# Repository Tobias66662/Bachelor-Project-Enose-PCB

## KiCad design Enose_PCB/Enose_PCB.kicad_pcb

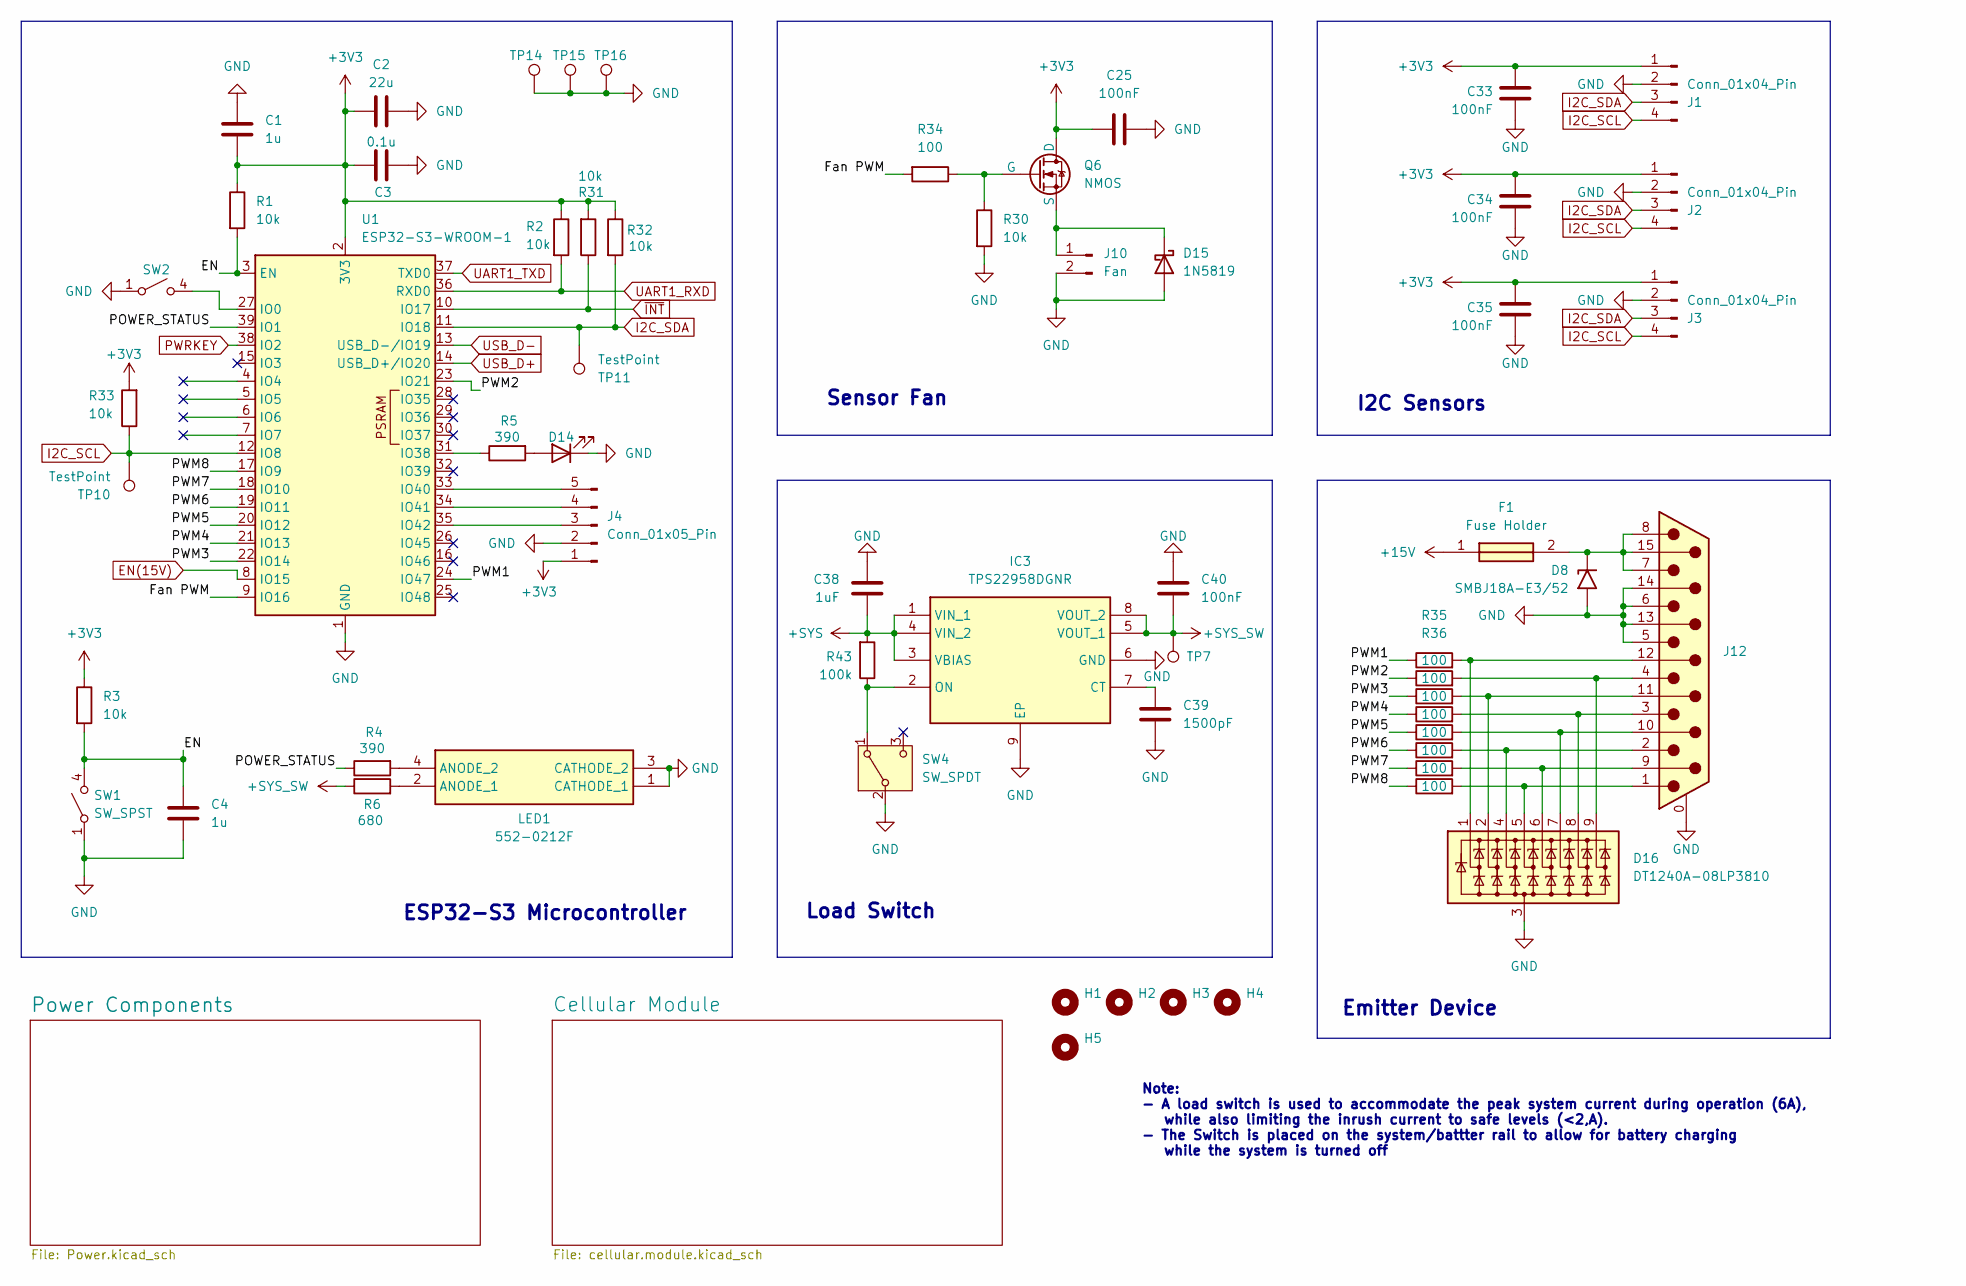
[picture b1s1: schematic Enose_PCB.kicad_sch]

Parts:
C1, C4: 1u; C_0805_2012Metric_Pad1.18x1.45mm_HandSolder
C2: 22u; C_0805_2012Metric_Pad1.18x1.45mm_HandSolder
C3: 0.1u; C_0805_2012Metric_Pad1.18x1.45mm_HandSolder
C25, C33, C34, C35, C40: 100nF; C_0805_2012Metric_Pad1.18x1.45mm_HandSolder
C38: 1uF; C_0805_2012Metric_Pad1.18x1.45mm_HandSolder
C39: 1500pF; C_0805_2012Metric_Pad1.18x1.45mm_HandSolder
D8: SMBJ18A-E3/52; D_SMB
D14: LED Amber; LED_0805_2012Metric_Pad1.15x1.40mm_HandSolder
D15: 1N5819; D_SOD-123
D16: DT1240A-08LP3810; UDFN-9_1.0x3.8mm_P0.5mm
F1: Fuse Holder; 64600001223; Mouser Part Number 576-64600001223
H1, H2, H3, H4, H5: MountingHole; MountingHole_3.2mm_M3
IC3: TPS22958DGNR; SOP65P490X110-9N; Mouser Part Number 595-TPS22958DGNR
J1: Conn_01x04_Pin; PinHeader_1x04_P2.54mm_Vertical
J2, J3: Conn_01x04_Pin; JST_XH_B4B-XH-A_1x04_P2.50mm_Vertical
J4: Conn_01x05_Pin; PinHeader_1x05_P2.54mm_Vertical
J10: Fan; JST_XH_B2B-XH-AM_1x02_P2.50mm_Vertical
J12: DA15_Pins_MountingHoles; 6E17C015PAJ121
LED1: 552-0212F; 5520212F; Mouser Part Number 645-552-0212F
Q6: NMOS; SOT-23-3
R1, R2, R3, R30, R31, R32, R33: 10k; R_0805_2012Metric_Pad1.20x1.40mm_HandSolder
R4, R5: 390; R_0805_2012Metric_Pad1.20x1.40mm_HandSolder
R6: 680; R_0805_2012Metric_Pad1.20x1.40mm_HandSolder
R34, R35, R36, R37, R38, R39, R40, R41, R42: 100; R_0805_2012Metric_Pad1.20x1.40mm_HandSolder
R43: 100k; R_0805_2012Metric_Pad1.20x1.40mm_HandSolder
SW1, SW2: SW_SPST; 430181038816
SW4: SW_SPDT; OS102011MA1QN1
TP7, TP10, TP11, TP14, TP15, TP16: TestPoint; TestPoint_Pad_D1.5mm
U1: ESP32-S3-WROOM-1

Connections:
+3V3: C1.1, C2.1, C3.2, C25.2, C33.1, C34.1, C35.1, J1.1, J2.1, J3.1, J4.1, Q6.1 (D), R1.1, R2.1, R3.1, R31.2, R32.1, R33.2, U1.2 (3V3); also elsewhere on the board
+15V: F1.1; also elsewhere on the board
+SYS: C38.2, IC3.1 (VIN_1), IC3.3 (VBIAS), IC3.4 (VIN_2), R43.2; also elsewhere on the board
+SYS_SW: C40.2, IC3.5 (VOUT_1), IC3.8 (VOUT_2), R6.1, TP7.1; also elsewhere on the board
/EN: C4.1, R1.2, R3.2, SW1.4 (B), U1.3 (EN)
/Fan PWM: R34.2, U1.9 (IO16)
/POWER_STATUS: R4.1, U1.39 (IO1)
/PWM1: R35.1, U1.24 (IO47)
/PWM2: R36.1, U1.23 (IO21)
/PWM3: R37.1, U1.22 (IO14)
/PWM4: R38.1, U1.21 (IO13)
/PWM5: R39.1, U1.20 (IO12)
/PWM6: R40.1, U1.19 (IO11)
/PWM7: R41.1, U1.18 (IO10)
/PWM8: R42.1, U1.17 (IO9)
EN(15V): U1.8 (IO15); also elsewhere on the board
GND: C1.2, C2.2, C3.1, C4.2, C25.1, C33.2, C34.2, C35.2, C38.1, C39.2, C40.1, D8.2 (A2), D14.1 (K), D15.2 (A), D16.3 (A), IC3.6 (GND), IC3.9 (EP), J1.2, J2.2, J3.2, J4.2, J10.2, J12.0 (PAD), J12.5, J12.6, J12.13, J12.14, LED1.1 (CATHODE_1), LED1.3 (CATHODE_2), R30.2, SW1.1 (A), SW2.1 (A), SW4.2 (B), TP14.1, TP15.1, TP16.1, U1.1 (GND), U1.40 (GND), U1.41 (GND); also elsewhere on the board
I2C_SCL: J1.4, J2.4, J3.4, R33.1, TP10.1, U1.12 (IO8); also elsewhere on the board
I2C_SDA: J1.3, J2.3, J3.3, R32.2, TP11.1, U1.11 (IO18); also elsewhere on the board
unnamed: D8.1 (A1), F1.2, J12.7, J12.8, J12.15
unnamed: D14.2 (A), R5.2
unnamed: D15.1 (K), J10.1, Q6.3 (S)
unnamed: D16.1 (K1), J12.12, R35.2
unnamed: D16.2 (K2), J12.11 (P111), R37.2
unnamed: D16.4 (K3), J12.2, R40.2
unnamed: D16.5 (K4), J12.1, R42.2
unnamed: D16.6 (K5), J12.9, R41.2
unnamed: D16.7 (K6), J12.10, R39.2
unnamed: D16.8 (K7), J12.3, R38.2
unnamed: D16.9 (K8), J12.4, R36.2
unnamed: C39.1, IC3.7 (CT)
unnamed: IC3.2 (ON), R43.1, SW4.1 (A)
unnamed: J4.3, U1.35 (IO42)
unnamed: J4.4, U1.34 (IO41)
unnamed: J4.5, U1.33 (IO40)
unnamed: LED1.2 (ANODE_1), R6.2
unnamed: LED1.4 (ANODE_2), R4.2
unnamed: Q6.2 (G), R30.1, R34.1
unnamed: SW2.4 (B), U1.27 (IO0)
unnamed: R5.1, U1.31 (IO38)
PWRKEY: U1.38 (IO2); also elsewhere on the board
UART1_RXD: R2.2, U1.36 (RXD0); also elsewhere on the board
UART1_TXD: U1.37 (TXD0); also elsewhere on the board
USB_D+: U1.14 (USB_D+/IO20); also elsewhere on the board
USB_D-: U1.13 (USB_D-/IO19); also elsewhere on the board
~INT: R31.1, U1.10 (IO17); also elsewhere on the board

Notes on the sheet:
Note: - A load switch is used to accommodate the peak system current during operation (6A), while also limiting the inrush current to safe levels (<2,A). - The Switch is placed on the system/battter rail to allow for battery charging while the system is turned off
ESP32-S3 Microcontroller
Emitter Device
Load Switch
I2C Sensors
Sensor Fan

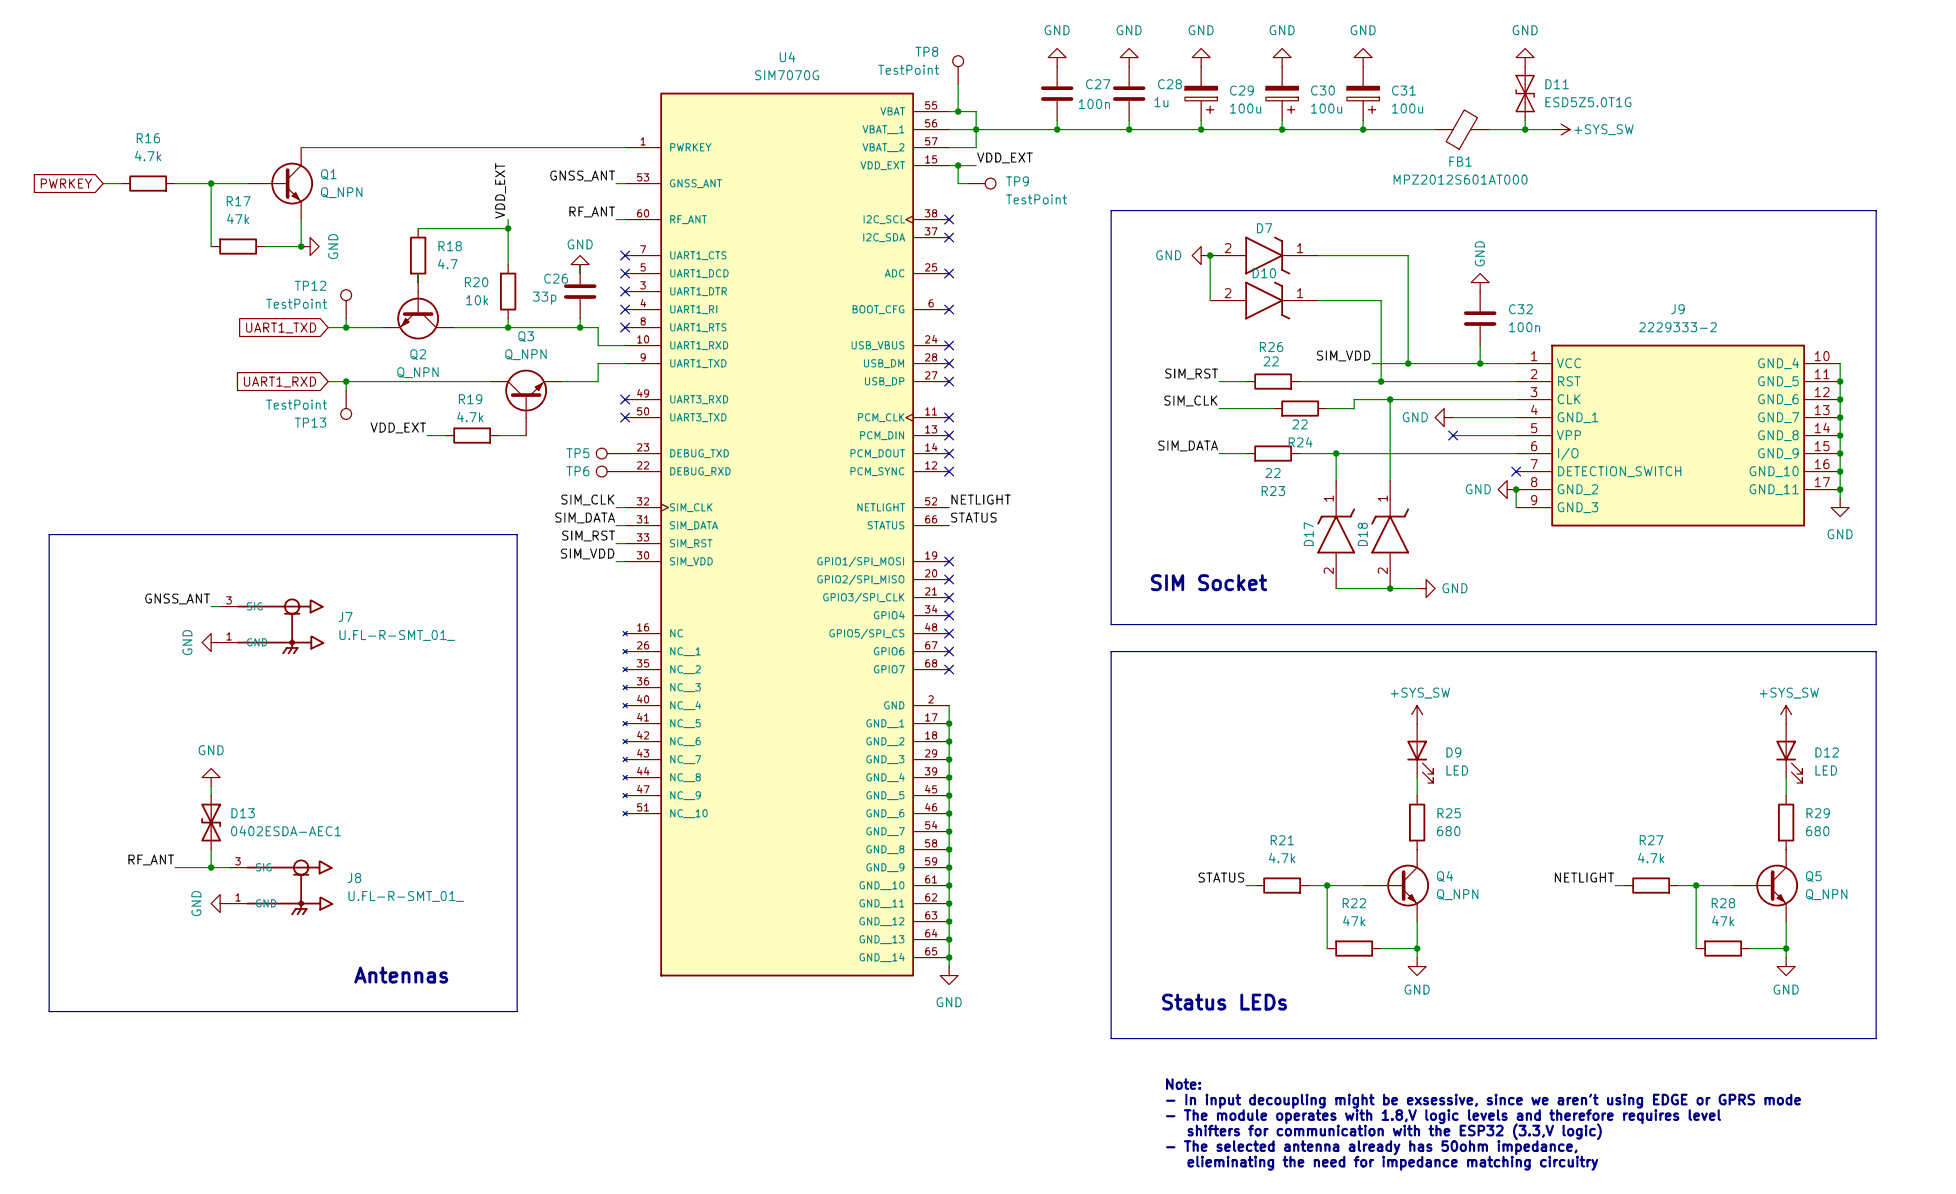
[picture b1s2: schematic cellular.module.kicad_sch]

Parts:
C26: 33p; C_0603_1608Metric_Pad1.08x0.95mm_HandSolder
C27, C32: 100n; C_0805_2012Metric_Pad1.18x1.45mm_HandSolder
C28: 1u; C_0805_2012Metric_Pad1.18x1.45mm_HandSolder
C29, C30, C31: 100u; CAPAE530X610N
D7, D10, D17, D18: ESD8351XV2T1G; SODFL1608X70N; Mouser Part Number 863-ESD8351XV2T1G
D9, D12: LED; LED_0805_2012Metric_Pad1.15x1.40mm_HandSolder
D11: ESD5Z5.0T1G; D_SOD-523
D13: 0402ESDA-AEC1; 0402ESDAAEC1
FB1: MPZ2012S601AT000; L_0805_2012Metric_Pad1.05x1.20mm_HandSolder
J7, J8: U.FL-R-SMT_01_; HRS_U.FL-R-SMT_01_
J9: 2229333-2; 22293332; Mouser Part Number 571-2229333-2
Q1, Q2, Q3, Q4, Q5: Q_NPN; SOT96P237X111-3N
R16, R19, R21, R27: 4.7k; R_0805_2012Metric_Pad1.20x1.40mm_HandSolder
R17, R22, R28: 47k; R_0805_2012Metric_Pad1.20x1.40mm_HandSolder
R18: 4.7; R_0805_2012Metric_Pad1.20x1.40mm_HandSolder
R20: 10k; R_0805_2012Metric_Pad1.20x1.40mm_HandSolder
R23, R24, R26: 22; R_0805_2012Metric_Pad1.20x1.40mm_HandSolder
R25, R29: 680; R_0805_2012Metric_Pad1.20x1.40mm_HandSolder
TP5, TP6, TP8, TP9, TP12, TP13: TestPoint; TestPoint_Pad_D1.5mm
U4: SIM7070G; MODULE_SIM7070G; PARTREV V1.03

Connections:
+SYS_SW: D9.2 (A), D11.1 (A1), D12.2 (A), FB1.2; also elsewhere on the board
/Cellular Module/GNSS_ANT: J7.3 (SIG), U4.53 (GNSS_ANT)
/Cellular Module/NETLIGHT: R27.1, U4.52 (NETLIGHT)
/Cellular Module/RF_ANT: D13.2 (A2), J8.3 (SIG), U4.60 (RF_ANT)
/Cellular Module/SIM_CLK: R24.2, U4.32 (SIM_CLK)
/Cellular Module/SIM_DATA: R23.2, U4.31 (SIM_DATA)
/Cellular Module/SIM_RST: R26.1, U4.33 (SIM_RST)
/Cellular Module/SIM_VDD: C32.2, D7.1 (K), J9.1 (VCC), U4.30 (SIM_VDD)
/Cellular Module/STATUS: R21.1, U4.66 (STATUS)
/Cellular Module/VDD_EXT: R18.1, R19.1, R20.2, TP9.1, U4.15 (VDD_EXT)
GND: C26.1, C27.1, C28.1, C29.2, C30.2, C31.2, C32.1, D7.2 (A), D10.2 (A), D11.2 (A2), D13.1 (A1), D17.2 (A), D18.2 (A), J7.1 (GND), J7.2 (GND), J8.1 (GND), J8.2 (GND), J9.4 (GND_1), J9.8 (GND_2), J9.9 (GND_3), J9.10 (GND_4), J9.11 (GND_5), J9.12 (GND_6), J9.13 (GND_7), J9.14 (GND_8), J9.15 (GND_9), J9.16 (GND_10), J9.17 (GND_11), Q1.2 (E), Q4.2 (E), Q5.2 (E), R17.1, R22.1, R28.1, U4.2 (GND), U4.17 (GND__1), U4.18 (GND__2), U4.29 (GND__3), U4.39 (GND__4), U4.45 (GND__5), U4.46 (GND__6), U4.54 (GND__7), U4.58 (GND__8), U4.59 (GND__9), U4.61 (GND__10), U4.62 (GND__11), U4.63 (GND__12), U4.64 (GND__13), U4.65 (GND__14); also elsewhere on the board
unnamed: D9.1 (K), R25.1
unnamed: D10.1 (K), J9.2 (RST), R26.2
unnamed: D12.1 (K), R29.1
unnamed: D17.1 (K), J9.6 (I/O), R23.1
unnamed: D18.1 (K), J9.3 (CLK), R24.1
unnamed: Q1.1 (B), R16.2, R17.2
unnamed: Q1.3 (C), U4.1 (PWRKEY)
unnamed: Q2.1 (B), R18.2
unnamed: C26.2, Q2.3 (C), R20.1, U4.10 (UART1_RXD)
unnamed: Q3.1 (B), R19.2
unnamed: Q3.2 (E), U4.9 (UART1_TXD)
unnamed: Q4.1 (B), R21.2, R22.2
unnamed: Q4.3 (C), R25.2
unnamed: Q5.1 (B), R27.2, R28.2
unnamed: Q5.3 (C), R29.2
unnamed: TP6.1, U4.22 (DEBUG_RXD)
unnamed: TP5.1, U4.23 (DEBUG_TXD)
unnamed: C27.2, C28.2, C29.1, C30.1, C31.1, FB1.1, TP8.1, U4.55 (VBAT), U4.56 (VBAT__1), U4.57 (VBAT__2)
PWRKEY: R16.1; also elsewhere on the board
UART1_RXD: Q3.3 (C), TP13.1; also elsewhere on the board
UART1_TXD: Q2.2 (E), TP12.1; also elsewhere on the board

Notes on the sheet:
SIM Socket
Status LEDs
Antennas
Note: - In input decoupling might be exsessive, since we aren't using EDGE or GPRS mode - The module operates with 1.8,V logic levels and therefore requires level shifters for communication with the ESP32 (3.3,V logic) - The selected antenna already has 50ohm impedance, elieminating the need for im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

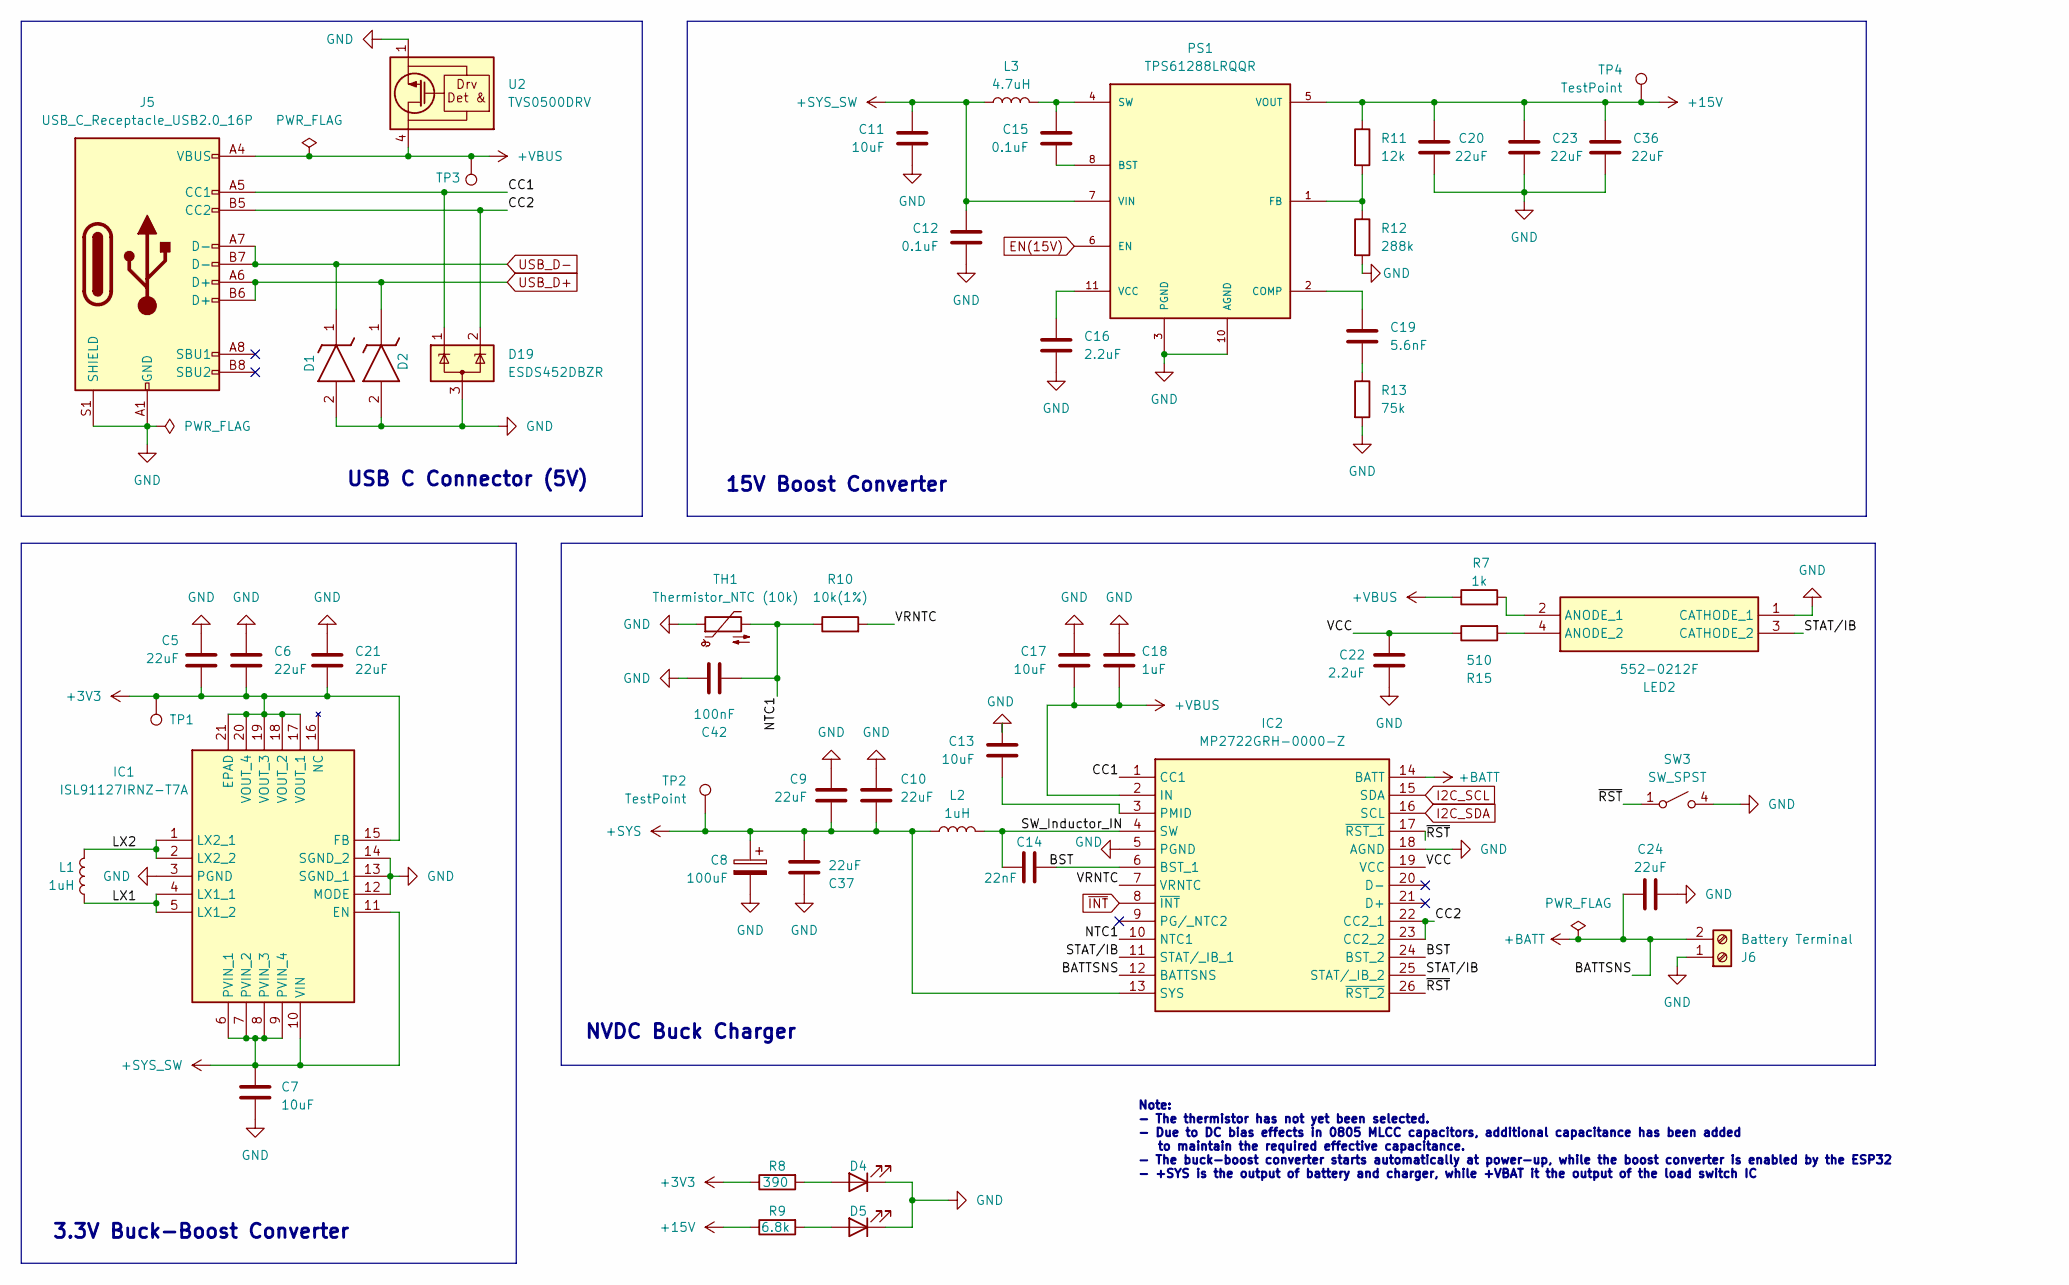
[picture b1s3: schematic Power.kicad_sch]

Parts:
C5, C6, C9, C10, C21, C24, C37: 22uF; C_0805_2012Metric_Pad1.18x1.45mm_HandSolder
C7, C11, C13, C17: 10uF; C_0805_2012Metric_Pad1.18x1.45mm_HandSolder
C8: 100uF; CAPAE530X610N
C12, C15: 0.1uF; C_0805_2012Metric_Pad1.18x1.45mm_HandSolder
C14: 22nF; C_0805_2012Metric_Pad1.18x1.45mm_HandSolder
C16, C22: 2.2uF; C_0805_2012Metric_Pad1.18x1.45mm_HandSolder
C18: 1uF; C_0805_2012Metric_Pad1.18x1.45mm_HandSolder
C19: 5.6nF; C_0805_2012Metric_Pad1.18x1.45mm_HandSolder
C20, C23, C36: 22uF; C_1210_3225Metric_Pad1.33x2.70mm_HandSolder
C42: 100nF; C_0805_2012Metric_Pad1.18x1.45mm_HandSolder
D1, D2: ESD8351XV2T1G; SODFL1608X70N; Mouser Part Number 863-ESD8351XV2T1G
D4, D5: LED GREEN; LED_0805_2012Metric_Pad1.15x1.40mm_HandSolder
D19: ESDS452DBZR; SOT-23-3
IC1: ISL91127IRNZ-T7A; QFN50P400X400X100-21N; Manufacturer_Part_Number ISL91127IRNZ-T7A; Mouser Part Number 968-ISL91127IRNZ-T7A
IC2: MP2722GRH-0000-Z; MP2722GRH0000Z; Mouser Part Number 946-MP2722GRH-0000-Z
J5: USB_C_Receptacle_USB2.0_16P; USB_C_Receptacle_GCT_USB4105-xx-A_16P_TopMnt_Horizontal
J6: Battery Terminal; TerminalBlock_Phoenix_PT-1,5-2-3.5-H_1x02_P3.50mm_Horizontal
L1: 1uH; SRP4030FA1R0M
L2: 1uH; INDPM5355X310N
L3: 4.7uH; L_Coilcraft_XAL6060-XXX
LED2: 552-0212F; 5520212F; Mouser Part Number 645-552-0212F
PS1: TPS61288LRQQR; CONV_TPS61288LRQQR; PARTREV C
R7: 1k; R_0805_2012Metric_Pad1.20x1.40mm_HandSolder
R8: 390; R_0805_2012Metric_Pad1.20x1.40mm_HandSolder
R9: 6.8k; R_0805_2012Metric_Pad1.20x1.40mm_HandSolder
R10: 10k(1%); R_0805_2012Metric_Pad1.20x1.40mm_HandSolder
R11: 12k; R_0805_2012Metric_Pad1.20x1.40mm_HandSolder
R12: 288k; R_0805_2012Metric_Pad1.20x1.40mm_HandSolder
R13: 75k; R_0805_2012Metric_Pad1.20x1.40mm_HandSolder
R15: 510; R_0805_2012Metric_Pad1.20x1.40mm_HandSolder
SW3: SW_SPST; 430181038816
TH1: Thermistor_NTC (10k); JST_XH_B2B-XH-AM_1x02_P2.50mm_Vertical
TP1, TP2, TP3, TP4: TestPoint; TestPoint_Pad_D1.5mm
U2: TVS0500DRV; WSON-6-1EP_2x2mm_P0.65mm_EP1x1.6mm

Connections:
+3V3: C5.2, C6.2, C21.2, IC1.15 (FB), IC1.17 (VOUT_1), IC1.18 (VOUT_2), IC1.19 (VOUT_3), IC1.20 (VOUT_4), IC1.21 (EPAD), R8.1, TP1.1; also elsewhere on the board
+15V: C20.1, C23.1, C36.1, PS1.5 (VOUT), R9.1, R11.1, TP4.1; also elsewhere on the board
+BATT: C24.2, IC2.12 (BATTSNS), IC2.14 (BATT), J6.2
+SYS: C8.1, C9.1, C10.2, C37.1, IC2.13 (SYS), L2.1, TP2.1; also elsewhere on the board
+SYS_SW: C7.1, C11.1, C12.1, IC1.6 (PVIN_1), IC1.7 (PVIN_2), IC1.8 (PVIN_3), IC1.9 (PVIN_4), IC1.10 (VIN), IC1.11 (EN), L3.1, PS1.7 (VIN); also elsewhere on the board
+VBUS: C17.1, C18.2, IC2.2 (IN), J5.A4 (VBUS), J5.A9 (VBUS), J5.B4 (VBUS), J5.B9 (VBUS), R7.1, TP3.1, U2.4 (IN), U2.5 (IN), U2.6 (IN)
/Power Components/BST: C14.2, IC2.6 (BST_1), IC2.24 (BST_2)
/Power Components/CC1: D19.1 (K), IC2.1 (CC1), J5.A5 (CC1)
/Power Components/CC2: D19.2 (K), IC2.22 (CC2_1), IC2.23 (CC2_2), J5.B5 (CC2)
/Power Components/LX1: IC1.4 (LX1_1), IC1.5 (LX1_2), L1.2
/Power Components/LX2: IC1.1 (LX2_1), IC1.2 (LX2_2), L1.1
/Power Components/NTC1: C42.2, IC2.10 (NTC1), R10.1, TH1.2
/Power Components/STAT/IB: IC2.11 (STAT/_IB_1), IC2.25 (STAT/_IB_2), LED2.3 (CATHODE_2)
/Power Components/SW_Inductor_IN: C14.1, IC2.4 (SW), L2.2
/Power Components/VCC: C22.1, IC2.19 (VCC), R15.1
/Power Components/VRNTC: IC2.7 (VRNTC), R10.2
/Power Components/~RST: IC2.17 (~RST_1), IC2.26 (~RST_2), SW3.1 (A)
EN(15V): PS1.6 (EN); also elsewhere on the board
GND: C5.1, C6.1, C7.2, C8.2, C9.2, C10.1, C11.2, C12.2, C13.2, C16.2, C17.2, C18.1, C20.2, C21.1, C22.2, C23.2, C24.1, C36.2, C37.2, C42.1, D1.2 (A), D2.2 (A), D4.1 (K), D5.1 (K), D19.3 (A), IC1.3 (PGND), IC1.12 (MODE), IC1.13 (SGND_1), IC1.14 (SGND_2), IC2.5 (PGND), IC2.18 (AGND), J5.A1 (GND), J5.A12 (GND), J5.B1 (GND), J5.B12 (GND), J5.S1 (SHIELD), J6.1, LED2.1 (CATHODE_1), PS1.3 (PGND), PS1.10 (AGND), R12.2, R13.2, SW3.4 (B), TH1.1, U2.1 (GND), U2.2 (GND), U2.3 (GND), U2.7 (GND); also elsewhere on the board
I2C_SCL: IC2.15 (SDA); also elsewhere on the board
I2C_SDA: IC2.16 (SCL); also elsewhere on the board
unnamed: C15.1, L3.2, PS1.4 (SW), PS1.9 (SW)
unnamed: C19.2, R13.1
unnamed: D4.2 (A), R8.2
unnamed: D5.2 (A), R9.2
unnamed: C13.1, IC2.3 (PMID)
unnamed: LED2.2 (ANODE_1), R7.2
unnamed: LED2.4 (ANODE_2), R15.2
unnamed: C15.2, PS1.8 (BST)
unnamed: C19.1, PS1.2 (COMP)
unnamed: PS1.1 (FB), R11.2, R12.1
unnamed: C16.1, PS1.11 (VCC)
USB_D+: D2.1 (K), J5.A6 (D+), J5.B6 (D+); also elsewhere on the board
USB_D-: D1.1 (K), J5.A7 (D-), J5.B7 (D-); also elsewhere on the board
~INT: IC2.8 (~INT); also elsewhere on the board

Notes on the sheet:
15V Boost Converter
3.3V Buck-Boost Converter
Note: - The thermistor has not yet been selected. - Due to DC bias effects in 0805 MLCC capacitors, additional capacitance has been added to maintain the required effective capacitance. - The buck-boost converter starts automatically at power-up, while the boost converter is enabled by the ESP32 - 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
USB C Connector (5V)
NVDC Buck Charger

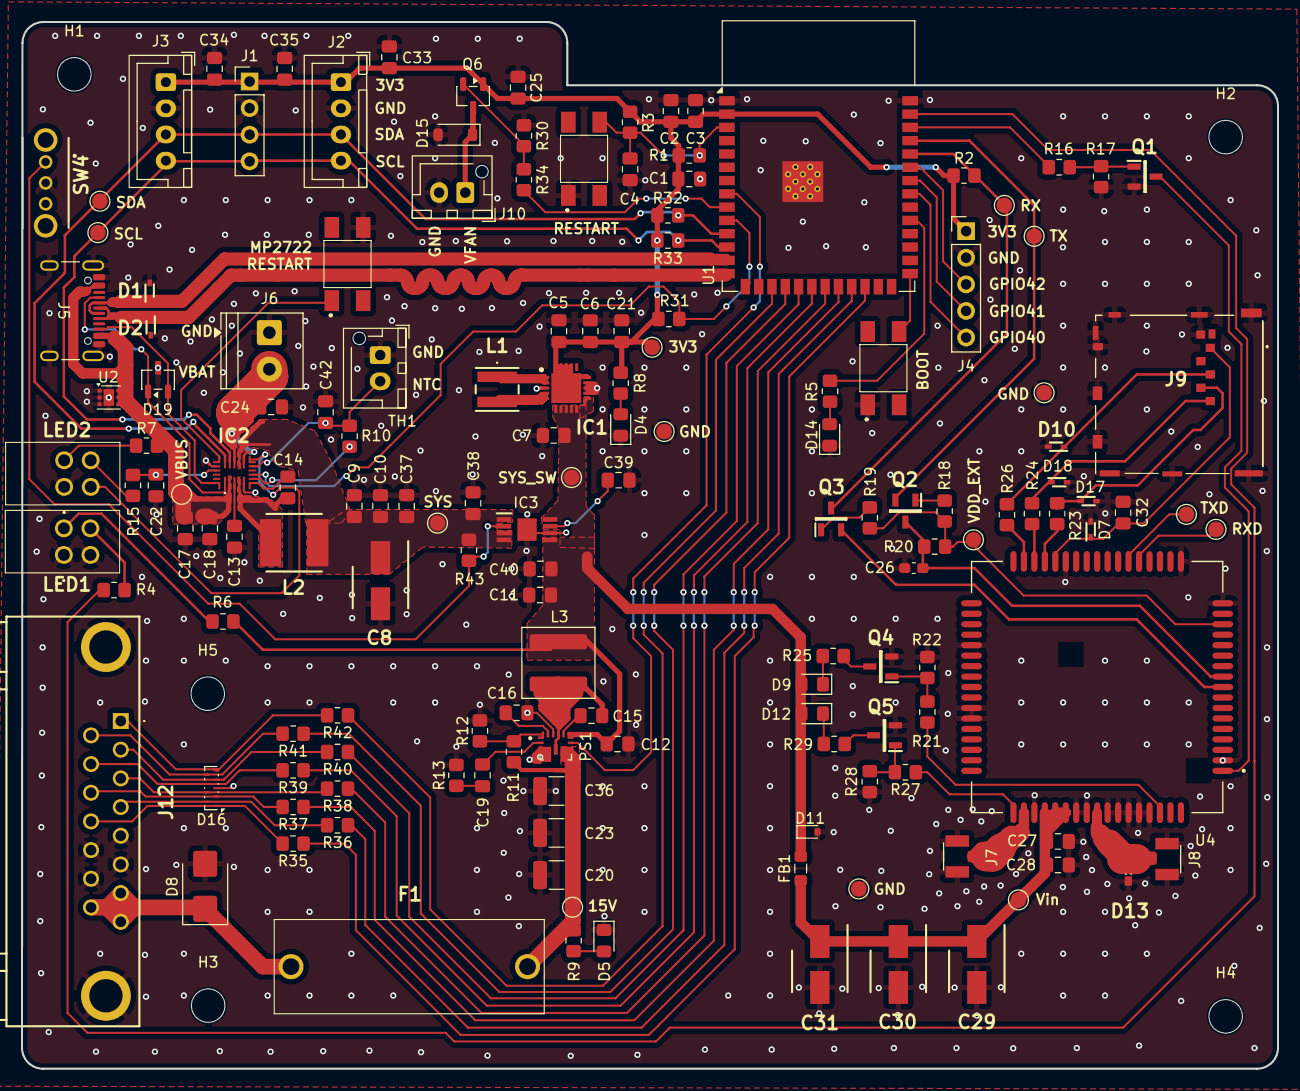
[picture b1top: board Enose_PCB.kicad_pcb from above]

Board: 2 copper layers, 120.0 x 100.0 mm, 157 parts (0 on the bottom side), 97 nets.

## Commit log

2026-03-03 added some connectors
2026-03-04 adding my pcb to the repo
2026-03-04 testing comment change on pcb to play with git pushing
2026-03-05 Added footprints
2026-03-06 pushing some changes only a bit to go
2026-03-19 Changed power symbols
2026-03-20 Added something idk
2026-03-20 last emitter pcb changes
2026-04-04 Working on Enose PCB Layout
2026-04-05 removed backup folder from git
2026-04-05 Finished placeing components for Enose PCB
2026-04-07 Added so netlabels
2026-04-09 Enose PCB almost done
2026-04-09 PCB almost done
2026-04-12 Enose PCB almost done, just needs ground vias
2026-04-14 Enose board ready for review
2026-04-17 Enose PCB finished
